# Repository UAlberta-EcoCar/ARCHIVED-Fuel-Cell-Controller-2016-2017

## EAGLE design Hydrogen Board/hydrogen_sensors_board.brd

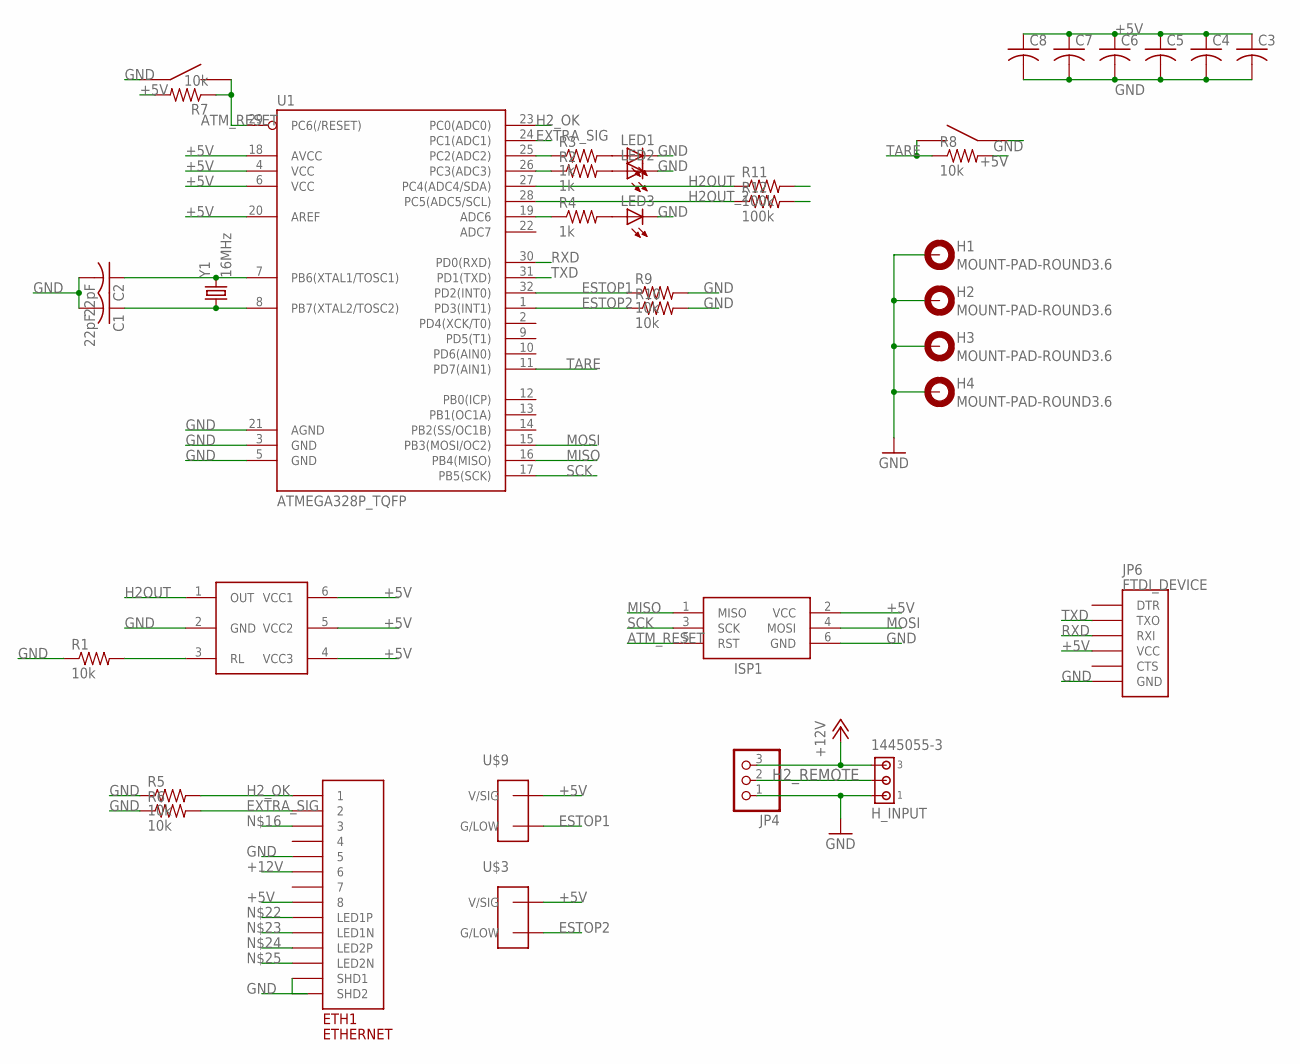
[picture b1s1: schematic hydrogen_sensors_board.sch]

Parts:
C1, C2: 22pF; C0603K
C3, C4, C5, C6, C7, C8: C-USC0603; C0603
ETH1: ETHERNET; A122645-ND
H1, H2, H3, H4: MOUNT-PAD-ROUND3.6; 3,6-PAD
H_INPUT: 1445055-3
ISP1: AVRISP-BOX
JP4: PINHD-1X3; 1X03
JP6: FTDI_DEVICE; FTDI_DEVICE_SIDE
LED1, LED2, LED3: LEDCHIPLED_0805; CHIPLED_0805
R1, R5, R6, R7, R8, R9, R10: 10k; 0603-RES
R2, R3, R4: 1k; 0603-RES
R11, R12: 100k; 0603-RES
U1: ATMEGA328P_TQFP; TQFP32-08
U$1: MQ-8MQ-8; MQ-8
U$2, U$10: EG4621CT-ND
U$3, U$9: TE770966; 2X1-MATE-N-LOCK
Y1: 16MHz; HC49US

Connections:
+5V: C3.1, C4.1, C5.1, C6.1, C7.1, C8.1, ETH1.P$8 (8), ISP1.2 (VCC), JP6.P$4 (VCC), R7.2, R8.2, U1.4 (VCC), U1.6 (VCC), U1.18 (AVCC), U1.20 (AREF), U$1.4 (VCC3), U$1.5 (VCC2), U$1.6 (VCC1), U$3.CIRCUIT1 (V/SIG), U$9.CIRCUIT1 (V/SIG)
+12V: ETH1.P$6 (6), H_INPUT.3, JP4.3
ATM_RESET: ISP1.5 (RST), R7.1, U1.29 (PC6(/RESET)), U$10.P$3, U$10.P$4
ESTOP1: R9.1, U1.32 (PD2(INT0)), U$9.CIRCUIT2 (G/LOW)
ESTOP2: R10.1, U1.1 (PD3(INT1)), U$3.CIRCUIT2 (G/LOW)
EXTRA_SIG: ETH1.P$2 (2), R6.2, U1.24 (PC1(ADC1))
GND: C1.2, C2.2, C3.2, C4.2, C5.2, C6.2, C7.2, C8.2, ETH1.P$5 (5), H1.B3,6, H2.B3,6, H3.B3,6, H4.B3,6, H_INPUT.1, ISP1.6 (GND), JP4.1, JP6.P$6 (GND), LED1.C, LED2.C, LED3.C, R1.1, R5.1, R6.1, R9.2, R10.2, R11.2, R12.2, U1.3 (GND), U1.5 (GND), U1.21 (AGND), U$1.2 (GND), U$2.P$1, U$2.P$2, U$10.P$1, U$10.P$2
H2OUT: R11.1, U1.27 (PC4(ADC4/SDA)), U$1.1 (OUT)
H2OUT_2: R12.1, U1.28 (PC5(ADC5/SCL))
H2_OK: ETH1.P$1 (1), R5.2, U1.23 (PC0(ADC0))
H2_REMOTE: H_INPUT.2, JP4.2
MISO: ISP1.1 (MISO), U1.16 (PB4(MISO))
MOSI: ISP1.4 (MOSI), U1.15 (PB3(MOSI/OC2))
unnamed: C2.1, U1.7 (PB6(XTAL1/TOSC1)), Y1.2
unnamed: R1.2, U$1.3 (RL)
unnamed: C1.1, U1.8 (PB7(XTAL2/TOSC2)), Y1.1
unnamed: R3.1, U1.25 (PC2(ADC2))
unnamed: R2.1, U1.26 (PC3(ADC3))
unnamed: R4.1, U1.19 (ADC6)
unnamed: LED1.A, R3.2
unnamed: LED2.A, R2.2
unnamed: LED3.A, R4.2
unnamed: ETH1.P$13 (SHD1), ETH1.P$14 (SHD2)
RXD: JP6.P$3 (RXI), U1.30 (PD0(RXD))
SCK: ISP1.3 (SCK), U1.17 (PB5(SCK))
TARE: R8.1, U1.11 (PD7(AIN1)), U$2.P$3, U$2.P$4
TXD: JP6.P$2 (TXO), U1.31 (PD1(TXD))

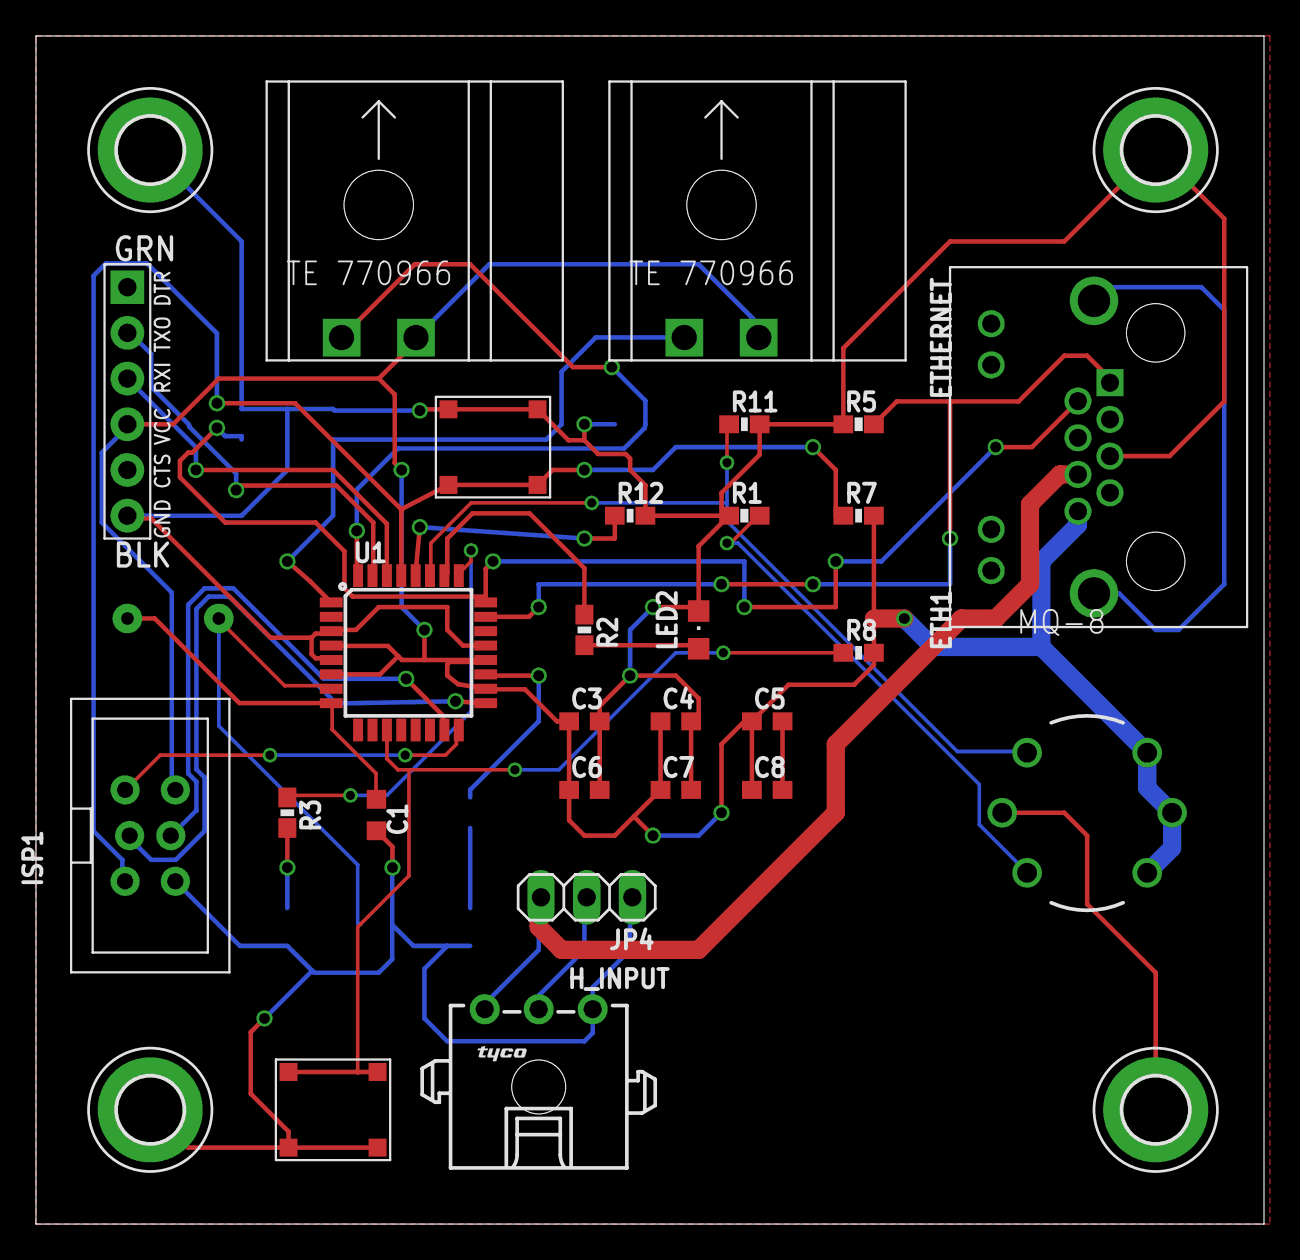
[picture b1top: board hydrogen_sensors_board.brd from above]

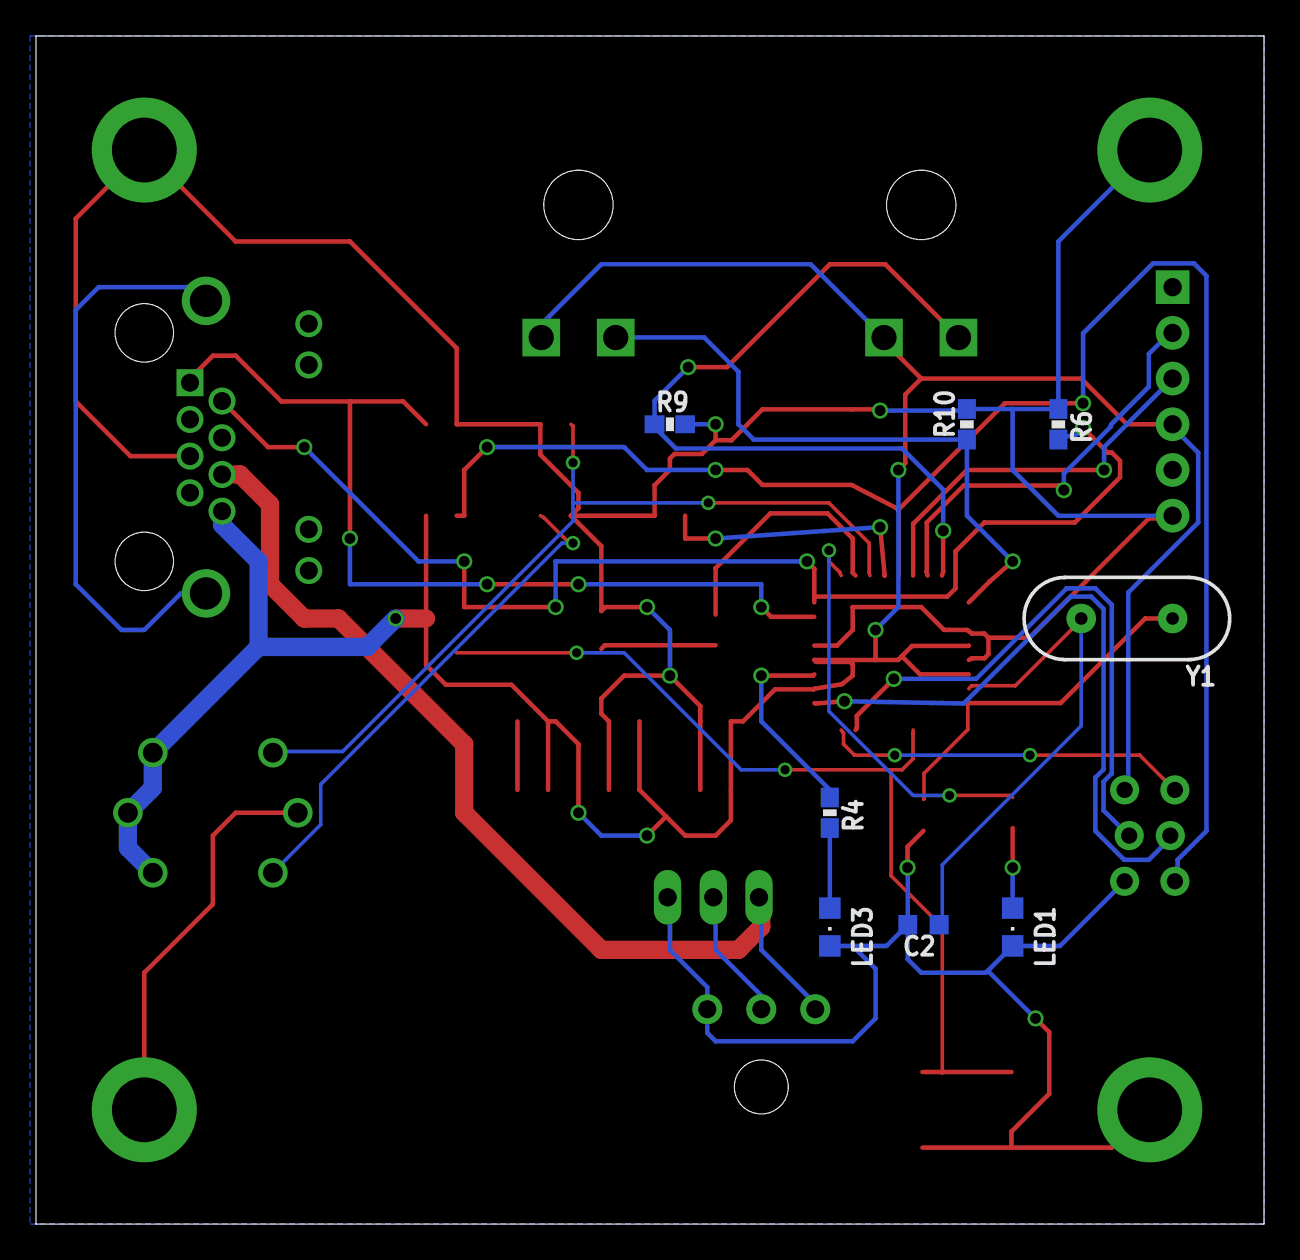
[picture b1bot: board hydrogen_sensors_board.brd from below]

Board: 2 copper layers, 68.2 x 66.0 mm, 39 parts (8 on the bottom side), 27 nets.

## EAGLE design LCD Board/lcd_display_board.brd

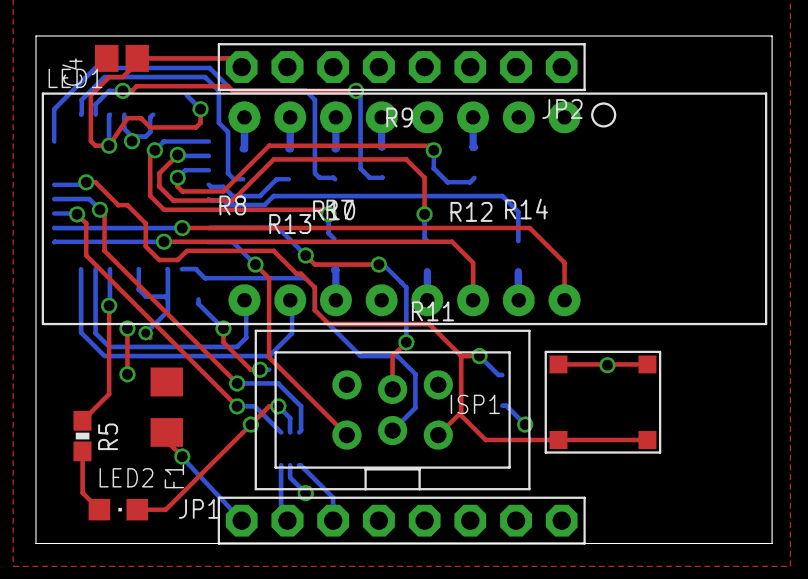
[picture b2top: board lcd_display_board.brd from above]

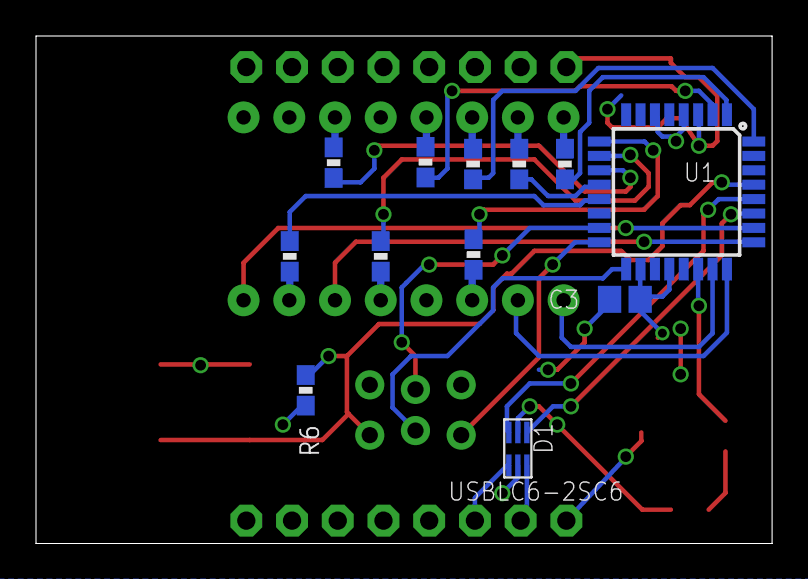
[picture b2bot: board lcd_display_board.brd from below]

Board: 2 copper layers, 40.9 x 28.2 mm, 21 parts (12 on the bottom side), 33 nets.

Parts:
C3: 1uF; C0805
C4: 0.1uF; C0805
D1: USBLC6-2SC6
F1: 1206
ISP1: AVRISP-BOX
JP1, JP2: 1X08-BIG
LED1: 7-SEGMENT-4DIGIT-YOUNGSUN
LED2: CHIPLED_0805
R5: 1k; 0603-RES
R6: 10k; 0603-RES
R7, R8, R9, R10, R11, R12, R13, R14: 80 Ohm; 0603-RES
U1: ATMEGA328P_TQFP; TQFP32-08
U$10: EG4621CT-ND

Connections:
+3.3V: C3.1, C4.1, D1.P$5, F1.1, R6.2, U1.4, U1.6, U1.18, U1.20
ATM_RESET: ISP1.5, R6.1, U1.29, U$10.P$3, U$10.P$4
DIG1AN: LED1.1, U1.23
DIG2AN: LED1.2, U1.24
DIG3AN: LED1.6, U1.25
DIG4AN: LED1.8, U1.26
GND: C3.2, C4.2, D1.P$2, ISP1.6, JP1.4, JP1.5, JP1.6, JP1.7, JP1.8, JP2.1, JP2.2, JP2.3, JP2.4, JP2.5, JP2.6, JP2.7, JP2.8, LED2.C, U1.3, U1.5, U1.21, U$10.P$1, U$10.P$2
MISO: ISP1.1, U1.16
MOSI: ISP1.4, U1.15
unnamed: F1.2, JP1.1
unnamed: D1.P$6, JP1.2
unnamed: R5.1, U1.22
unnamed: LED2.A, R5.2
unnamed: R7.1, U1.32
unnamed: R8.1, U1.1
unnamed: R9.1, U1.2
unnamed: R10.1, U1.9
unnamed: R11.1, U1.10
unnamed: R12.1, U1.11
unnamed: R13.1, U1.12
unnamed: R14.1, U1.13
unnamed: D1.P$4, JP1.3
SCK: ISP1.3, U1.17
SCL: D1.P$3, U1.28
SDA: D1.P$1, U1.27
SEGA: LED1.14, R7.2
SEGB: LED1.16, R8.2
SEGC: LED1.13, R9.2
SEGD: LED1.3, R10.2
SEGDP: LED1.7, R14.2
SEGE: LED1.5, R11.2
SEGF: LED1.11, R12.2
SEGG: LED1.15, R13.2

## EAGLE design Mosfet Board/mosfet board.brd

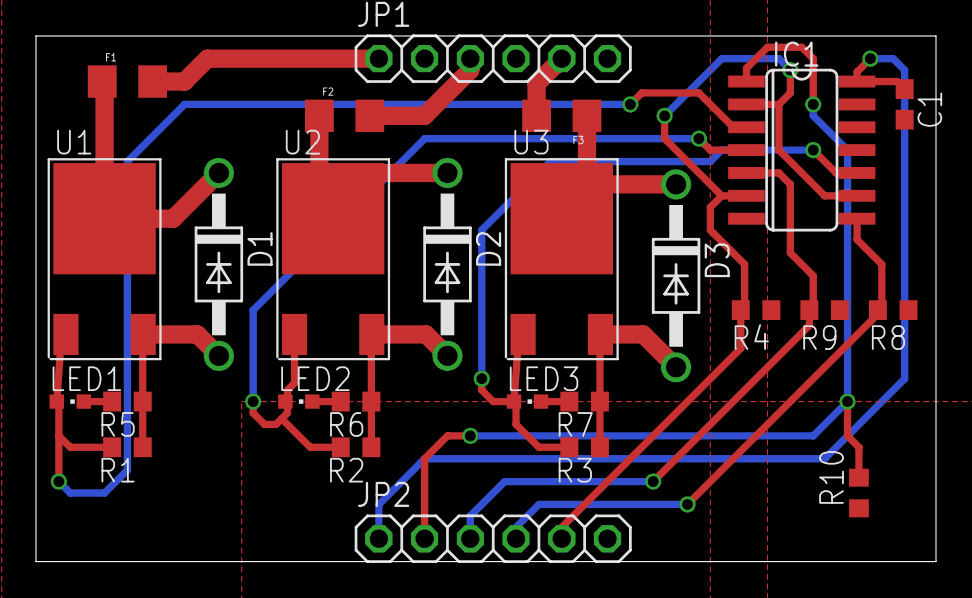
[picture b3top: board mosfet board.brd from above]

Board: 2 copper layers, 50.0 x 29.2 mm, 26 parts (0 on the bottom side), 19 nets.

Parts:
C1: C0603
D1: D1; DO41-10
D2: D2; DO41-10
D3: D3; DO41-10
F1, F2, F3: 1206
IC1: 4081D; SO14
JP1, JP2: 1X06
LED1, LED2, LED3: CHIPLED_0603
R1: R1; R0603
R2: R2; R0603
R3: R3; R0603
R4, R8, R9, R10: 10k; R0603
R5, R6, R7: 1k; R0603
U1: MOSFET1; MOSFET
U2: MOSFET2; MOSFET
U3: MOSFET3; MOSFET

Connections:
ESTOP: IC1.2, IC1.6, IC1.9, JP2.5, R4.2
GND: D1.A, D2.A, D3.A, JP1.2, JP1.4, JP1.6, R1.1, R2.1, R3.1, R5.1, R6.1, R7.1, U1.P$3, U2.P$3, U3.P$3
IN1: IC1.1, JP2.2, R10.2
IN2: IC1.5, JP2.3, R9.2
IN3: IC1.8, JP2.4, R8.2
unnamed: IC1.3, LED1.A, R1.2, U1.P$1
unnamed: IC1.4, LED2.A, R2.2, U2.P$1
unnamed: IC1.10, LED3.A, R3.2, U3.P$1
unnamed: F1.2, JP1.1
unnamed: F2.2, JP1.3
unnamed: F3.2, JP1.5
unnamed: LED1.C, R5.2
unnamed: LED2.C, R6.2
unnamed: LED3.C, R7.2
OUT1: D1.C, F1.1, U1.P$2
OUT2: D2.C, F2.1, U2.P$2
OUT3: D3.C, F3.1, U3.P$2
VDD: C1.1, IC1.14, JP2.1
VSS: C1.2, IC1.7, JP2.6, R4.1, R8.1, R9.1, R10.1

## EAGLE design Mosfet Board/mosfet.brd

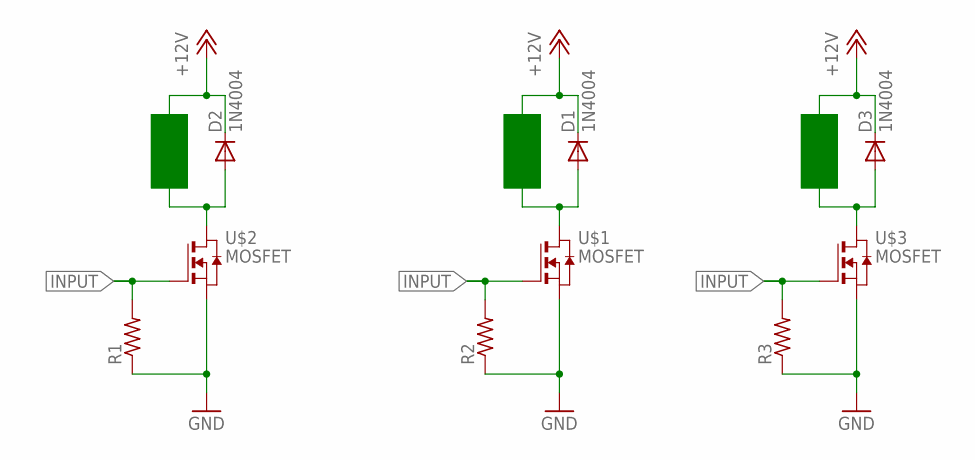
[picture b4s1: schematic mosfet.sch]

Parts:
D1, D2, D3: 1N4004; DO41-10
R1, R2, R3: R-US_R0603; R0603
U$1, U$2, U$3: MOSFET

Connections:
+12V: D1.C, D2.C, D3.C
GND: R1.1, R2.1, R3.1, U$1.P$3 (S), U$2.P$3 (S), U$3.P$3 (S)
unnamed: R2.2, U$1.P$1 (G)
unnamed: D1.A, U$1.P$2 (D)
unnamed: D2.A, U$2.P$2 (D)
unnamed: R1.2, U$2.P$1 (G)
unnamed: D3.A, U$3.P$2 (D)
unnamed: R3.2, U$3.P$1 (G)

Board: 2 copper layers, 9 parts (0 on the bottom side), 8 nets, no tracks yet.

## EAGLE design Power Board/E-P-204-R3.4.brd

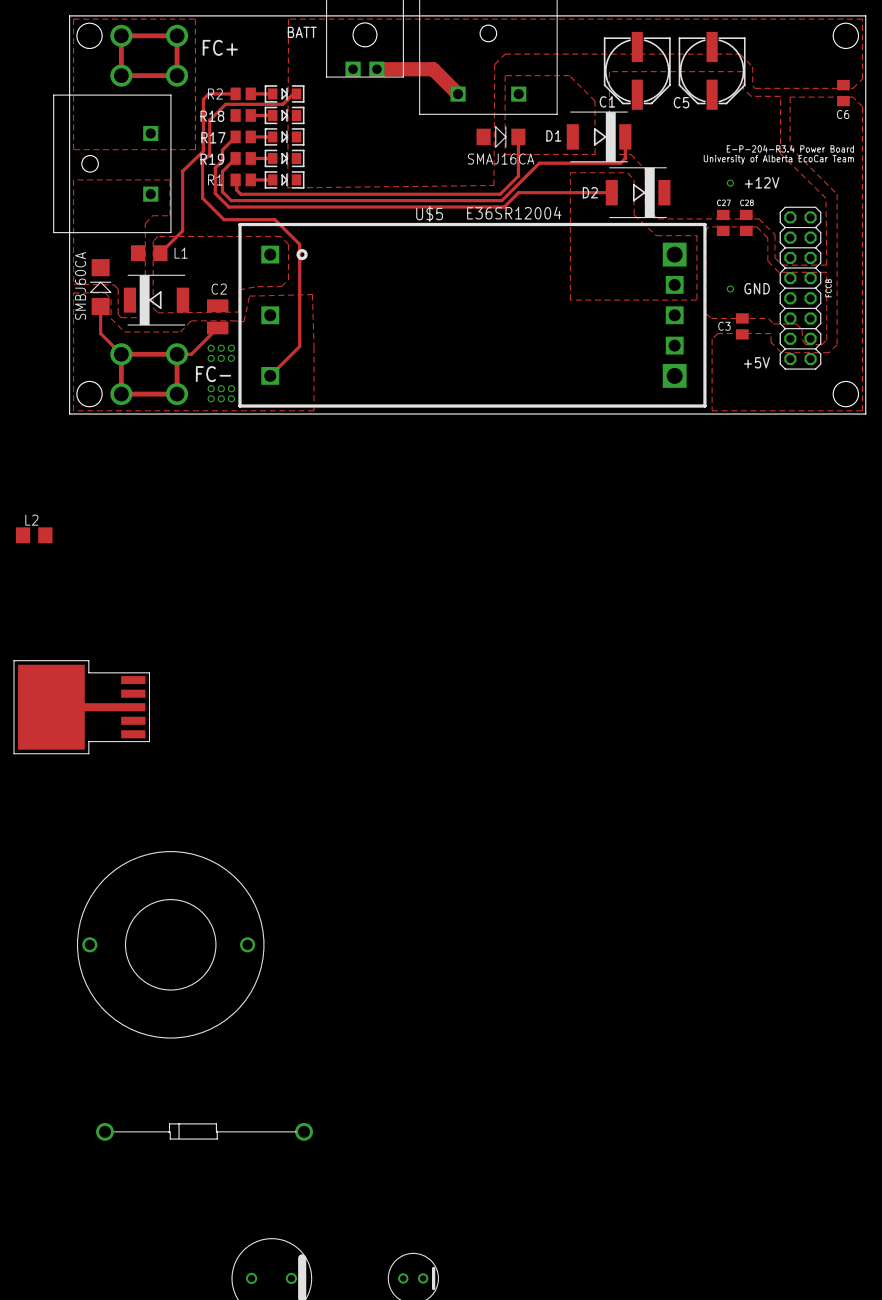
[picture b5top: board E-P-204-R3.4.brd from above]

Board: 2 copper layers, 100.0 x 50.0 mm, 36 parts (0 on the bottom side), 16 nets.

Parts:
C1, C5: 330u; PANASONIC_E
C2: 2.2u; C1210
C3, C6, C27, C28: 3.3uF; C0805K
D1, D2: VISHAY_SL43; DO-214AB_SMC
FCCB: 2X08
L1, L2: 270n; L3225P
LED1, LED2, LED4, LED5, LED6: LED-1206
R1, R17, R19: 500; M0805
R2: 2k; M0805
R18: 150; M0805
U$2: STPS5L60; STM_SMC
U$3: SMBJ60CA; .277X.089
U$4: SMAJ16CA; .25X.07
U$5: E36SR12004; 2.30X0.90X0.34
U$6, U$8: SCREW-8191
U$7, U$10: FUSEMINI-BLADE; MINI-BLADE-FUSE
U$9: MBR360GOS
U$12: 43650-0200
U$14: LM2576; D2PAK-5
U$15: CAPESK107M025AC3AA; ESK107M025AC3AA
U$16: CAPESK108M025AH4EA; ESK108M025AH4EA
U$17: M1418-ND

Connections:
5V_OUT: C3.1, C6.1, FCCB.15, FCCB.16, R18.2, U$14.4, U$16.P$1
12V_OUT: C1.+, C5.+, C27.1, C28.1, D1.C, D2.C, FCCB.1, FCCB.2, FCCB.3, FCCB.4, FCCB.5, FCCB.6, R19.2, U$14.1, U$15.P$1
BATT_12V: D1.A, R1.2, U$4.CATHODE, U$10.OUT
BATT_IN: U$10.IN, U$12.P$1
FC_12V: D2.A, R17.2, U$5.P$7, U$5.P$8
FC_48V: C2.1, L1.2, R2.2, U$2.A, U$5.P$1
FC_FUSED: L1.1, U$2.C, U$3.CATHODE, U$7.IN
FC_GND: L2.1, U$5.P$2, U$5.P$3
FC_IN: U$7.OUT, U$8.P$1, U$8.P$2, U$8.P$3, U$8.P$4
GND: C1.-, C2.2, C3.2, C5.-, C6.2, C27.2, C28.2, FCCB.7, FCCB.8, FCCB.9, FCCB.10, FCCB.11, FCCB.12, FCCB.14, L2.2, LED1.C, LED2.C, LED4.C, LED5.C, LED6.C, U$3.ANODE, U$4.ANODE, U$5.P$4, U$5.P$5, U$6.P$1, U$6.P$2, U$6.P$3, U$6.P$4, U$9.P$2, U$12.P$2, U$14.3, U$14.5, U$14.GROUND, U$15.P$2, U$16.P$2
unnamed: LED1.A, R1.1
unnamed: LED2.A, R2.1
unnamed: U$9.P$1, U$14.2, U$17.P$2
unnamed: LED4.A, R17.1
unnamed: LED5.A, R18.1
unnamed: LED6.A, R19.1

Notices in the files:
parts and their libraries:
SparkFun-Connectors: Licensing: Creative Commons ShareAlike 4.0 International - https://creativecommons.org/licenses/by-sa/4.0
SparkFun: Licensing: CC v3.0 Share-Alike You are welcome to use this library for commercial purposes.
